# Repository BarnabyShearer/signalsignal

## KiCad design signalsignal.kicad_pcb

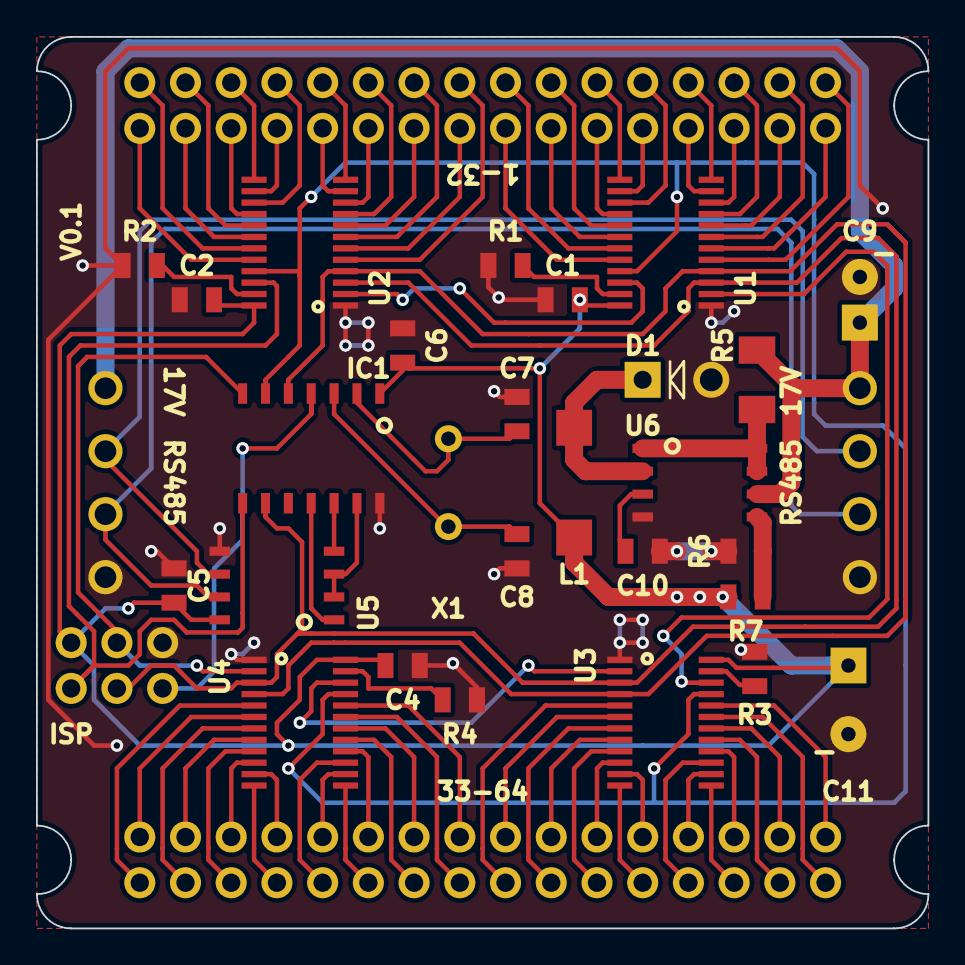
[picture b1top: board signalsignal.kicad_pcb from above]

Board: 2 copper layers, 49.5 x 49.5 mm, 32 parts (0 on the bottom side), 91 nets.

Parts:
C1, C2, C4, C5, C6: 0.1µF; SMD-0805
C7, C8: C; SMD-0805
C9: 100µF; Capacitor5x11RM2.5
C10: 470pF; SMD-0805
C11: 470µF; Capacitor8x13RM3.8
D1: DIODESCH; Diode_DO-41_SOD81_Vertical_AnodeUp
IC1: ATTINY841-SSU; SOIC-14_N
L1: 220µH; SELF-WE-PD3S
P1, P2: CONN_01X32; Pin_Header_Straight_2x16
P3: ISP; Pin_Header_Straight_2x03
P4, P5: CONN_01X04; RT063xxHBWC
R1, R2, R3, R4: R; SMD-0805
R5: 0.33; SMD-1206
R6: 1.2k; SMD-0805
R7: 3.8k; SMD-0805
U1, U2, U3, U4: TLC5928; SSOP-24
U5: SNx5176; SOIC-8-N
U6: MC34063; SOIC-8-N
X1: CRYSTAL; Crystal_HC49-U_Vertical

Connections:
+5V: C1.1, C2.1, C4.1, C5.1, C6.1, C11.1, IC1.1, L1.2, P3.2, R7.1, U1.24, U2.24, U3.24, U4.24, U5.8
/+17V: C9.1, P4.1, P5.4, R5.2, U6.6
/A: P4.2, P5.3, U5.6
/B: P4.3, P5.2, U5.7
/BLANK: IC1.6, U1.21, U2.21, U3.21, U4.21
/DIR: IC1.13, U5.2, U5.3
/LATCH: IC1.5, U1.4, U2.4, U3.4, U4.4
/MISO: IC1.8, P3.1, U2.22
/MOSI: IC1.7, P3.4, U4.2
/RESET: IC1.4, P3.5
/RX: IC1.11, U5.1
/SCK: IC1.9, P3.3, U1.3, U2.3, U3.3, U4.3
/TX: IC1.12, U5.4
/p1: P1.1, U2.20
/p2: P1.2, U2.19
/p3: P1.3, U2.18
/p4: P1.4, U2.17
/p5: P1.5, U2.16
/p6: P1.6, U2.13
/p7: P1.7, U2.14
/p8: P1.8, U2.15
/p9: P1.9, U2.11
/p10: P1.10, U2.12
/p11: P1.11, U2.10
/p12: P1.12, U2.9
/p13: P1.13, U2.8
/p14: P1.14, U2.7
/p15: P1.15, U2.6
/p16: P1.16, U2.5
/p17: P1.17, U1.20
/p18: P1.18, U1.19
/p19: P1.19, U1.18
/p20: P1.20, U1.17
/p21: P1.21, U1.16
/p22: P1.22, U1.13
/p23: P1.23, U1.14
/p24: P1.24, U1.15
/p25: P1.25, U1.11
/p26: P1.26, U1.12
/p27: P1.27, U1.10
/p28: P1.28, U1.9
/p29: P1.29, U1.8
/p30: P1.30, U1.7
/p31: P1.31, U1.6
/p32: P1.32, U1.5
/p33: P2.1, U3.20
/p34: P2.2, U3.19
/p35: P2.3, U3.18
/p36: P2.4, U3.17
/p37: P2.5, U3.16
/p38: P2.6, U3.13
/p39: P2.7, U3.14
/p40: P2.8, U3.15
/p41: P2.9, U3.11
/p42: P2.10, U3.12
/p43: P2.11, U3.10
/p44: P2.12, U3.9
/p45: P2.13, U3.8
/p46: P2.14, U3.7
/p47: P2.15, U3.6
/p48: P2.16, U3.5
/p49: P2.17, U4.20
/p50: P2.18, U4.19
/p51: P2.19, U4.18
/p52: P2.20, U4.17
/p53: P2.21, U4.16
/p54: P2.22, U4.13
/p55: P2.23, U4.14
/p56: P2.24, U4.15
/p57: P2.25, U4.11
/p58: P2.26, U4.12
/p59: P2.27, U4.10
/p60: P2.28, U4.9
/p61: P2.29, U4.8
/p62: P2.30, U4.7
/p63: P2.31, U4.6
/p64: P2.32, U4.5
GND: C1.2, C2.2, C4.2, C5.2, C6.2, C7.1, C8.1, C9.2, C10.2, C11.2, D1.1, IC1.14, P3.6, P4.4, P5.1, R1.2, R2.2, R3.2, R4.2, R6.2, U1.1, U2.1, U3.1, U4.1, U5.5, U6.4
unnamed: C7.2, IC1.2, X1.1
unnamed: C8.2, IC1.3, X1.2
unnamed: C10.1, U6.3
unnamed: D1.2, L1.1, U6.2
unnamed: R1.1, U1.23
unnamed: R2.1, U2.23
unnamed: R3.1, U3.23
unnamed: R4.1, U4.23
unnamed: R5.1, U6.1, U6.7, U6.8
unnamed: R6.1, R7.2, U6.5
unnamed: U1.2, U3.22
unnamed: U1.22, U2.2
unnamed: U3.2, U4.22

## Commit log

2014-12-31 init
2015-01-06 Switched to switcher
2015-01-06 tidy

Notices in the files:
signalsignal.kicad_pcb:
©2015 b@Zi.iS CC BY-SA
